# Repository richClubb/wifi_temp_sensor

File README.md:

WiFi Temp Sensor
----------------

A battery powered WiFi temperature sensor.

# Objectives

* Sub 10 GBP BOM cost
* Battery powered with a multiple month battery life
* Learn more about electronics
* Learn how to lay out PCBs
* USB charging integrated

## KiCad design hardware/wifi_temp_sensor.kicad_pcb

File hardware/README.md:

WiFI Temp Sensor Hardware
-------------------------

* Currently on KiCad 7

# Additional symbol and footprint libraries needed

* None

# BOM

* ESP8266 - https://www.bitsboxuk.com/index.php?main_page=product_info&cPath=302_312&products_id=2592
* LDO - https://www.mouser.co.uk/ProductDetail/Diodes-Incorporated/AZ1117CR-3.3TRG1?qs=FKu9oBikfSlEg7waHw2tMw%3D%3D
* SMD Capacitors - 10uF, 22uF - 
* PCB Sockets - 3 x 4 pin, 1 x 4+4 pin - https://www.bitsboxuk.com/index.php?main_page=index&cPath=225_230
* USB Micro B Socket - https://uk.rs-online.com/web/p/usb-connectors/1789510

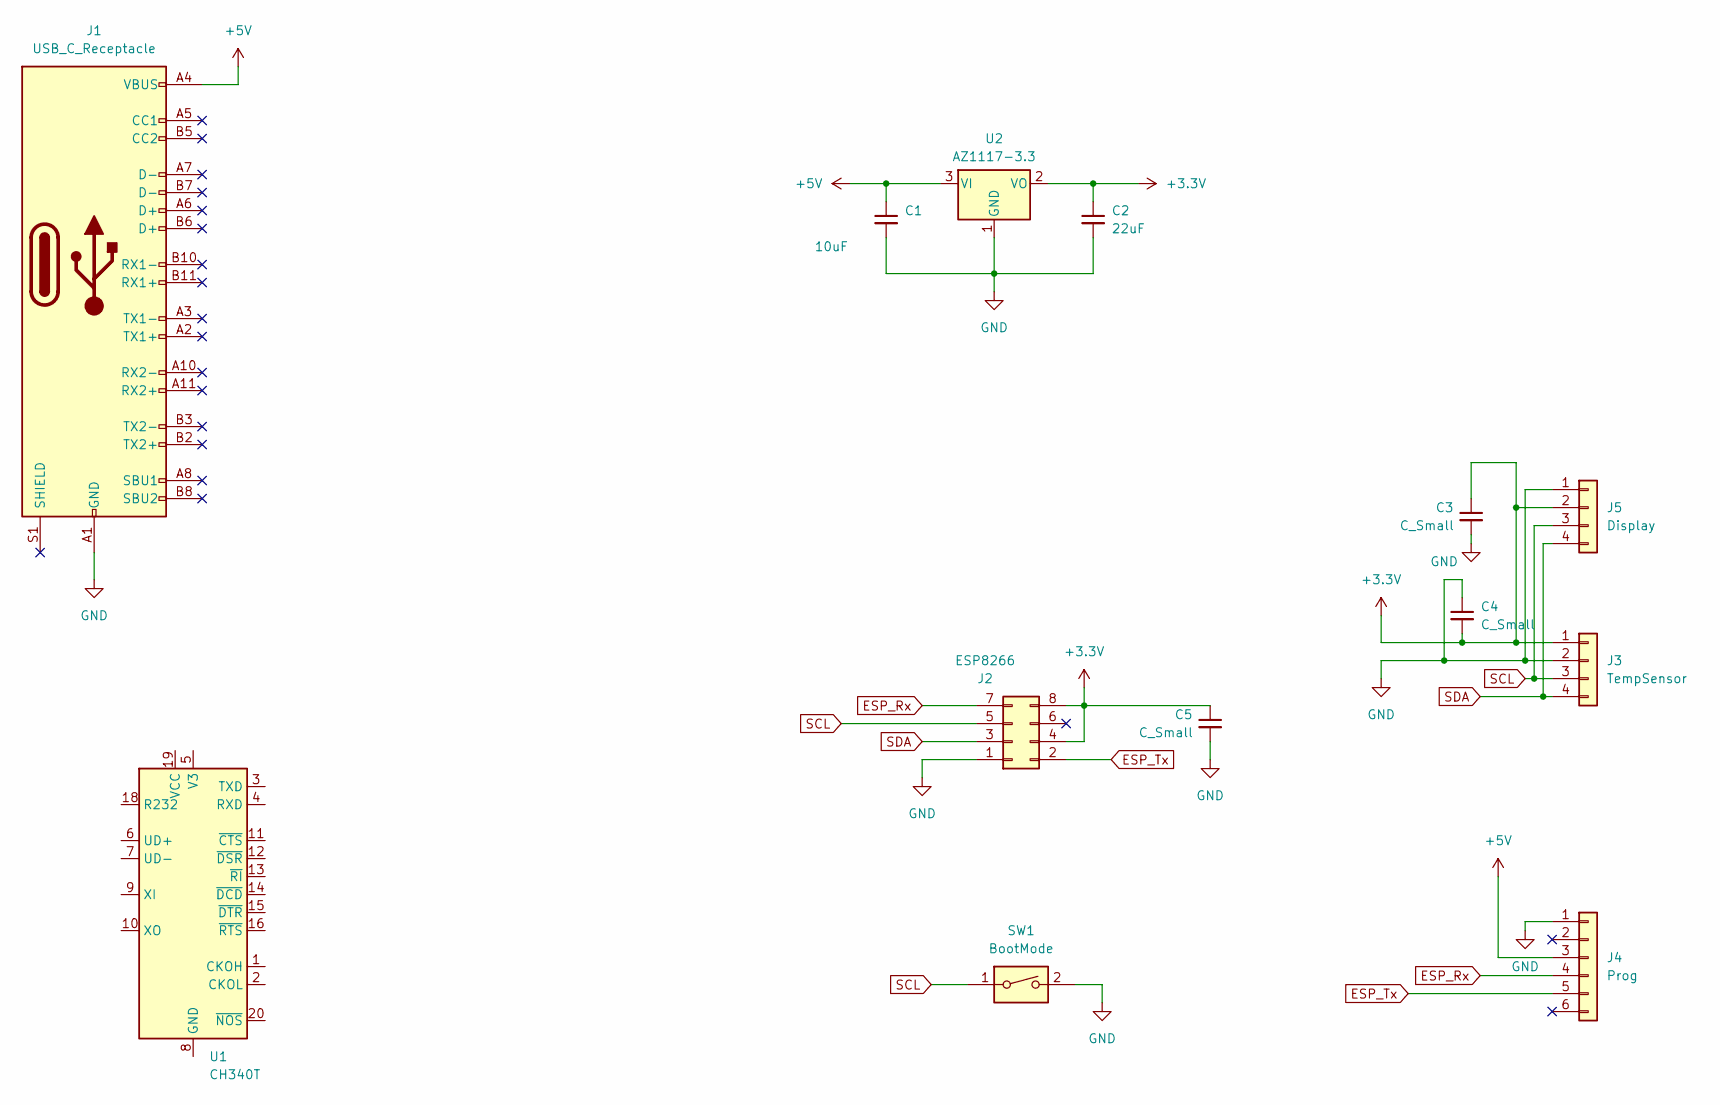
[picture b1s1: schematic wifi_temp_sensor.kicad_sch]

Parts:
C1: 10uF; C_1206_3216Metric_Pad1.33x1.80mm_HandSolder
C2: 22uF; C_1206_3216Metric_Pad1.33x1.80mm_HandSolder
C3, C4, C5: C_Small; C_1206_3216Metric_Pad1.33x1.80mm_HandSolder
J1: USB_C_Receptacle; USB_C_Receptacle_GCT_USB4105-xx-A_16P_TopMnt_Horizontal
J2: ESP8266; PinSocket_2x04_P2.54mm_Vertical
J3: TempSensor; PinSocket_1x04_P2.54mm_Vertical
J4: Prog; PinSocket_1x06_P2.54mm_Horizontal
J5: Display; PinSocket_1x04_P2.54mm_Vertical
SW1: BootMode; TL1105RA
U1: CH340T; SSOP-20_5.3x7.2mm_P0.65mm
U2: AZ1117-3.3; SOT-89-3_Handsoldering

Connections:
+3.3V: C2.1, C3.1, C4.2, C5.1, J2.4, J2.8, J3.1, J5.2, U2.2 (VO)
+5V: C1.1, J1.A4 (VBUS), J1.A9 (VBUS), J1.B4 (VBUS), J1.B9 (VBUS), J4.3, U2.3 (VI)
ESP_Rx: J2.7, J4.4
ESP_Tx: J2.2, J4.5
GND: C1.2, C2.2, C3.2, C4.1, C5.2, J1.A1 (GND), J1.A12 (GND), J1.B1 (GND), J1.B12 (GND), J2.1, J3.2, J4.1, J5.1, SW1.2, U2.1 (GND)
SCL: J2.5, J3.3, J5.3, SW1.1
SDA: J2.3, J3.4, J5.4

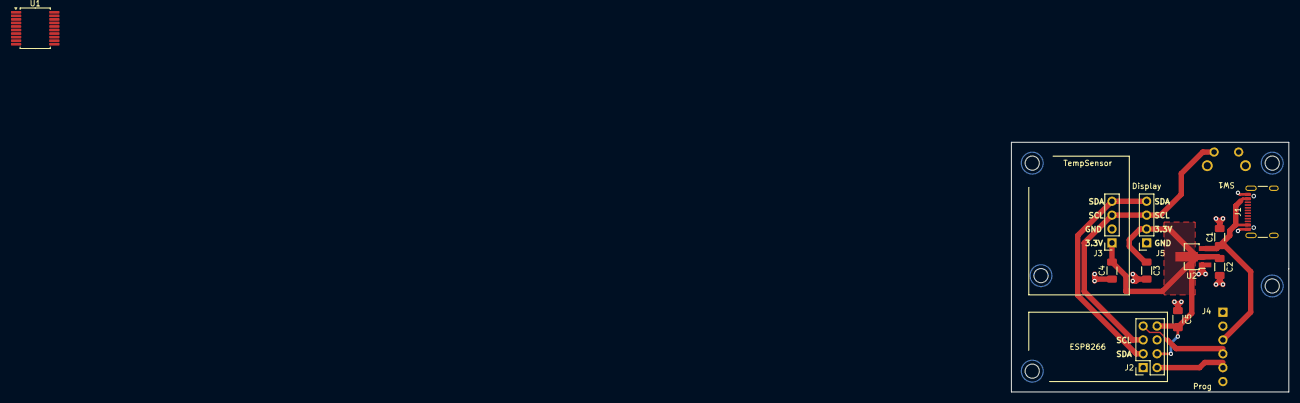
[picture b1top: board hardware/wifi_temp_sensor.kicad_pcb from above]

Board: 2 copper layers, 50.8 x 45.7 mm, 13 parts (1 on the bottom side), 7 nets.

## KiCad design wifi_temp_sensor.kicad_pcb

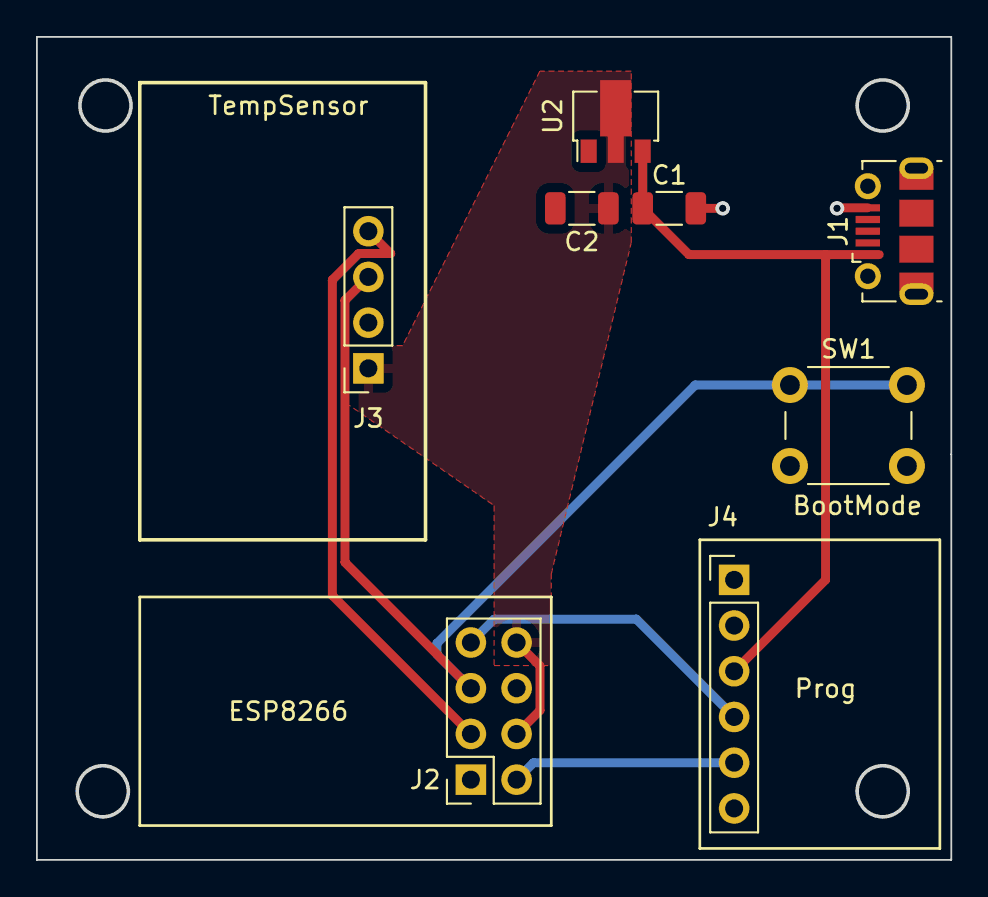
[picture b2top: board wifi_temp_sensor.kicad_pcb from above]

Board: 2 copper layers, 50.8 x 45.7 mm, 8 parts (0 on the bottom side), 7 nets.

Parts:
C1, C2: C_Small; C_1206_3216Metric
J1: USB_B_Mini; USB_Micro-B_Molex-105017-0001
J2: ESP8266; PinSocket_2x04_P2.54mm_Vertical
J3: TempSensor; PinSocket_1x04_P2.54mm_Vertical
J4: Prog; PinHeader_1x06_P2.54mm_Vertical
SW1: BootMode; SW_PUSH_6mm
U2: AZ1117-3.3; SOT-89-3

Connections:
+3.3V: C2.1, J2.4, J2.8, J3.1, U2.2 (VO)
+5V: C1.1, J1.1 (VBUS), J4.3, U2.3 (VI)
ESP_Rx: J2.7, J4.4
ESP_Tx: J2.2, J4.5
GND: C1.2, C2.2, J1.5 (GND), J2.1, J3.2, J4.1, SW1.2, U2.1 (GND)
SCL: J2.5, J3.3, SW1.1
SDA: J2.3, J3.4

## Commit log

2023-12-26 initial version 0.1, went out to JLCPCB in DEC 2023
2023-12-31 semi complete schematic
2023-12-31 gitignore
2023-12-31 added pdf of schematic
2024-01-04 fixes, still in progress
2024-01-04 Fixed minor issues and re-did the PCB
2024-01-04 minor fix
2024-01-05 mods
2024-01-06 Resized board and added LDO PSU
2024-01-06 Schematic changes to fix issues spotted with some suggestions and improvements
2024-01-06 Annotated and updated some of the PCB footprints
2024-01-07 Notes and initial PCB layout
2024-01-08 Reorg file structure
2024-01-08 V0.2
2024-01-08 added gitignore
2024-01-08 reorganised
2024-01-09 Tweaked the layout a little to improve routing.
2024-01-09 started layout for the USB section
2024-01-09 minor tweak to layout
2024-01-09 moved bootmode switch
2024-01-10 small re-route
2024-01-10 hardware readme update
2024-01-10 update firmware readme
2024-01-10 added enclosure folder
2024-01-10 removed unneeded files
2024-01-10 manual merge from esp32_msf_rcnotes
2024-01-10 Readme update
2024-01-11 cleanup
2024-01-13 finished initial PCB layout
2024-01-14 Small corrections
2024-01-14 corrected missing footprints
2024-01-15 Added text to back of board
2024-01-15 minor change to fit OLED screen connector
2024-01-15 fixed up small warnings on DRC, want to put in right angle switch
2024-01-15 fixed a few small issues, connected 3.3v to LEDs
2024-01-15 minor fixes
2024-01-17 Minor tweaks
2024-01-17 Sorting out BOM
2024-01-17 re-routed util switch to GPIO4 for deep sleep wakeup, re-routed USB to get the differental impedance to nearer to 90ohms
2024-01-17 Fixed up errors, ready for review
2024-01-17 minor changes
2024-01-21 Firmware update
2024-01-23 Final mods for V0.3, added right angle switch
2024-01-23 Gerber generation for V0_3. Production out 2024-01-23
2024-01-24 updated cache
2024-02-12 added .vscode to gitignore
2024-02-12 working firmware example
2024-07-11 Added utils and working MVP for the main sensor
2024-07-14 Added eeprom test
2024-07-15 Working example code with eeprom and serial command interface
2024-07-15 working code for programming password ssid and room and reconnect logic
2025-01-05 improved firmware
2025-01-05 Added in USB C Port to replace USB micro
2025-08-01 Don't really remember
